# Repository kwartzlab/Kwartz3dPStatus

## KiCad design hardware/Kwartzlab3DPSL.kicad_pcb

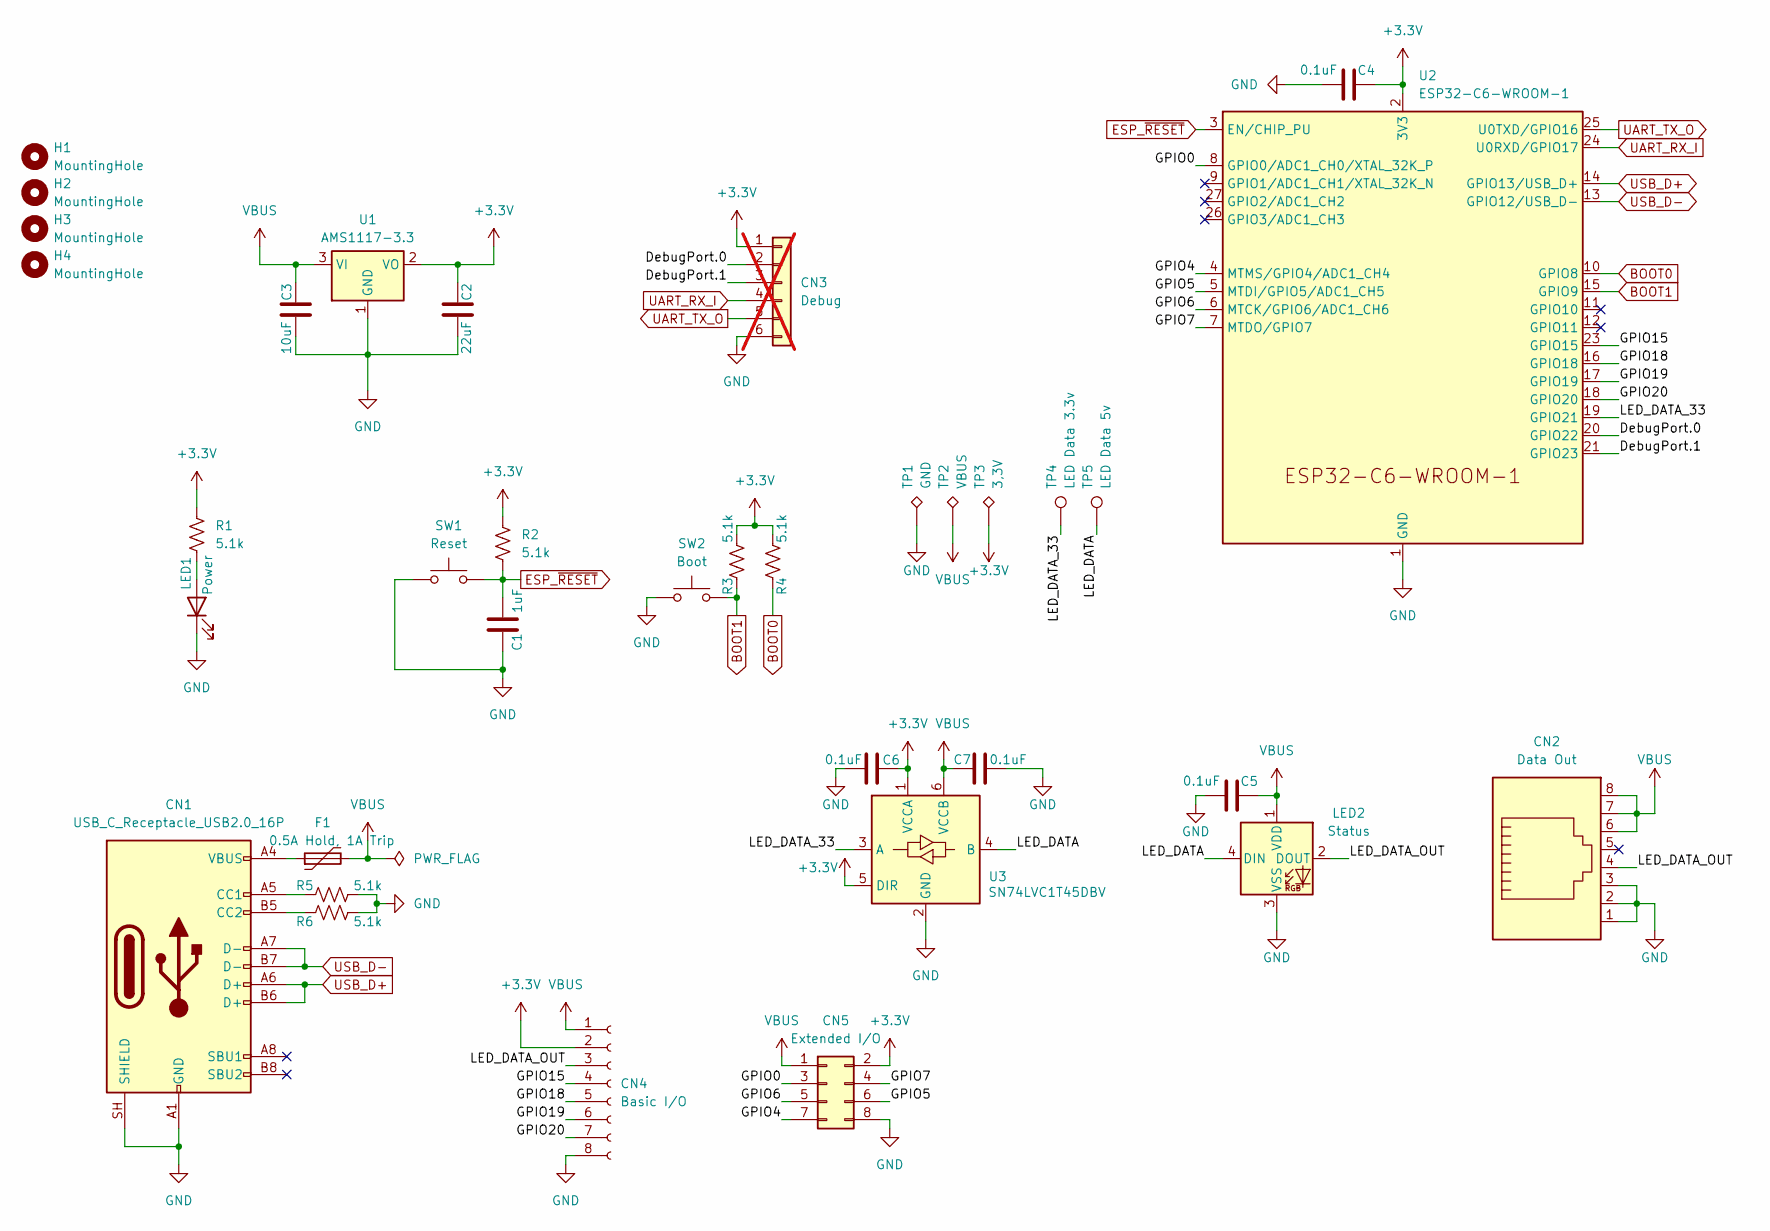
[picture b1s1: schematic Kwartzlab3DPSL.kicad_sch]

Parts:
C1: 1uF; C_0603_1608Metric
C2: 22uF; C_0603_1608Metric
C3: 10uF; C_0603_1608Metric
C4, C5, C6, C7: 0.1uF; C_0603_1608Metric
CN1: USB_C_Receptacle_USB2.0_16P; USB_C_Receptacle_G-Switch_GT-USB-7010ASV
CN2: Data Out; RJ45_AdamTech_MTJ-881X1
CN3: Debug; PinHeader_2x03_P1.00mm_Vertical; not fitted
CN4: Basic I/O; PhoenixContact_MC_1,5_8-G-3.5_1x08_P3.50mm_Horizontal
CN5: Extended I/O; PinHeader_2x04_P2.54mm_Vertical_SMD
F1: 0.5A Hold, 1A Trip; Fuse_2920_7451Metric
H1, H2, H3, H4: MountingHole; MountingHole_2.7mm_M2.5_ISO14580
LED1: Power; LED_0603_1608Metric
LED2: Status; LED_WS2812B_PLCC4_5.0x5.0mm_P3.2mm
R1, R2, R3, R4, R5, R6: 5.1k; R_0603_1608Metric
SW1: Reset; SW_SPST_PTS645Sx43SMTR92
SW2: Boot; SW_SPST_PTS645Sx43SMTR92
TP1: GND; TestPoint_THTPad_1.0x1.0mm_Drill0.5mm
TP2: VBUS; TestPoint_Pad_2.0x2.0mm
TP3: 3,3V; TestPoint_Pad_2.0x2.0mm
TP4: LED Data 3.3v; TestPoint_Pad_2.0x2.0mm
TP5: LED Data 5v; TestPoint_Pad_2.0x2.0mm
U1: AMS1117-3.3; SOT-223-3_TabPin2
U2: ESP32-C6-WROOM-1
U3: SN74LVC1T45DBV; SOT-23-6

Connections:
+3.3V: C2.2, C4.2, C6.2, CN3.1, CN4.2, CN5.2, R1.1, R2.1, R3.1, R4.1, TP3.1 (1_1), U1.2 (VO), U2.2 (3V3), U3.1 (VCCA), U3.5 (DIR)
/DebugPort.0: CN3.2, U2.20 (GPIO22)
/DebugPort.1: CN3.3, U2.21 (GPIO23)
/GPIO0: CN5.3, U2.8 (GPIO0/ADC1_CH0/XTAL_32K_P)
/GPIO4: CN5.7, U2.4 (MTMS/GPIO4/ADC1_CH4)
/GPIO5: CN5.6, U2.5 (MTDI/GPIO5/ADC1_CH5)
/GPIO6: CN5.5, U2.6 (MTCK/GPIO6/ADC1_CH6)
/GPIO7: CN5.4, U2.7 (MTDO/GPIO7)
/GPIO15: CN4.4, U2.23 (GPIO15)
/GPIO18: CN4.5, U2.16 (GPIO18)
/GPIO19: CN4.6, U2.17 (GPIO19)
/GPIO20: CN4.7, U2.18 (GPIO20)
/LED_DATA: LED2.4 (DIN), TP5.1 (1_1), U3.4 (B)
/LED_DATA_33: TP4.1 (1_1), U2.19 (GPIO21), U3.3 (A)
/LED_DATA_OUT: CN2.4, CN4.3, LED2.2 (DOUT)
BOOT0: R4.2, U2.10 (GPIO8)
BOOT1: R3.2, SW2.2, U2.15 (GPIO9)
ESP_~RESET: C1.1, R2.2, SW1.2, U2.3 (EN/CHIP_PU)
GND: C1.2, C2.1, C3.1, C4.1, C5.1, C6.1, C7.1, CN1.A1 (GND), CN1.A12 (GND), CN1.B1 (GND), CN1.B12 (GND), CN1.SH (SHIELD), CN2.1, CN2.2, CN2.3, CN3.6, CN4.8, CN5.8, LED1.1 (K), LED2.3 (VSS), R5.2, R6.2, SW1.1, SW2.1, TP1.1 (1_1), U1.1 (GND), U2.1 (GND), U2.28 (GND), U2.29 (GND), U3.2 (GND)
unnamed: CN1.A5 (CC1), R5.1
unnamed: CN1.B5 (CC2), R6.1
unnamed: CN1.A4 (VBUS), CN1.A9 (VBUS), CN1.B4 (VBUS), CN1.B9 (VBUS), F1.1
unnamed: LED1.2 (A), R1.2
UART_RX_I: CN3.4, U2.24 (U0RXD/GPIO17)
UART_TX_O: CN3.5, U2.25 (U0TXD/GPIO16)
USB_D+: CN1.A6 (D+), CN1.B6 (D+), U2.14 (GPIO13/USB_D+)
USB_D-: CN1.A7 (D-), CN1.B7 (D-), U2.13 (GPIO12/USB_D-)
VBUS: C3.2, C5.2, C7.2, CN2.6, CN2.7, CN2.8, CN4.1, CN5.1, F1.2, LED2.1 (VDD), TP2.1 (1_1), U1.3 (VI), U3.6 (VCCB)

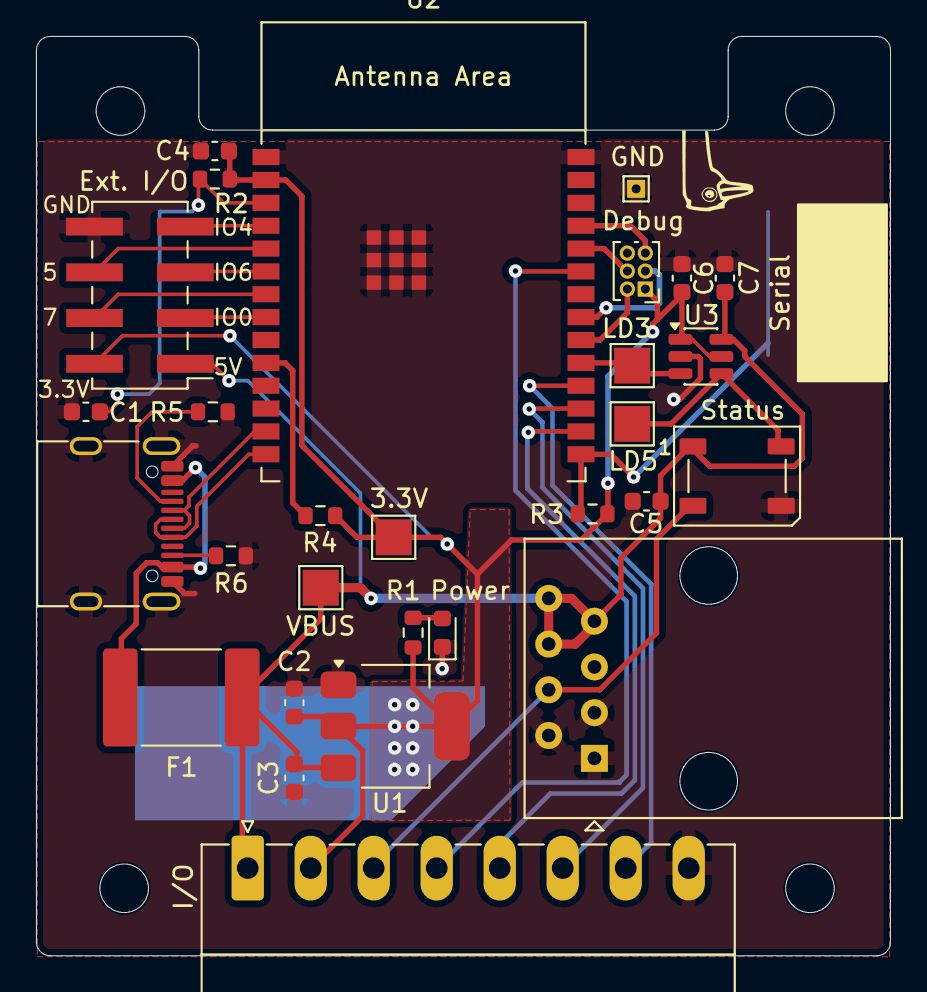
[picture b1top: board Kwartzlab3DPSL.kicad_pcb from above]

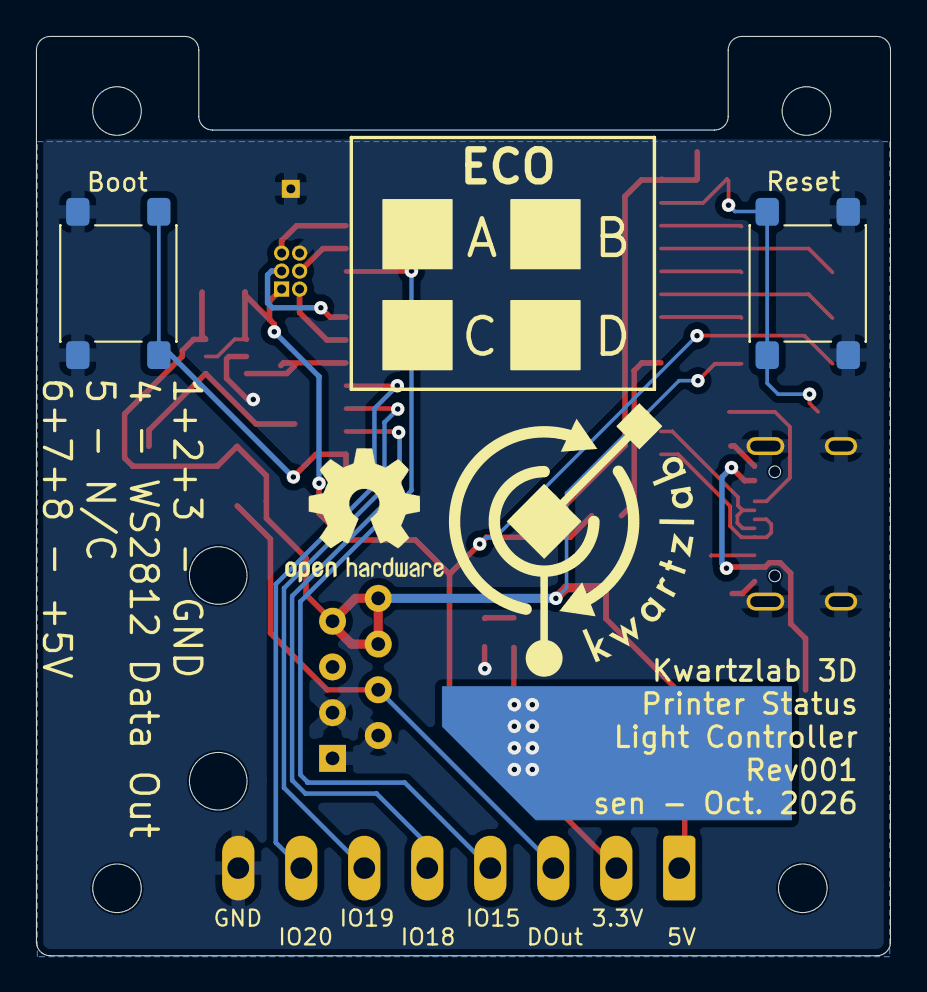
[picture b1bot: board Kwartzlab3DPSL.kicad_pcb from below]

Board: 2 copper layers, 47.4 x 51.1 mm, 35 parts (2 on the bottom side), 28 nets.

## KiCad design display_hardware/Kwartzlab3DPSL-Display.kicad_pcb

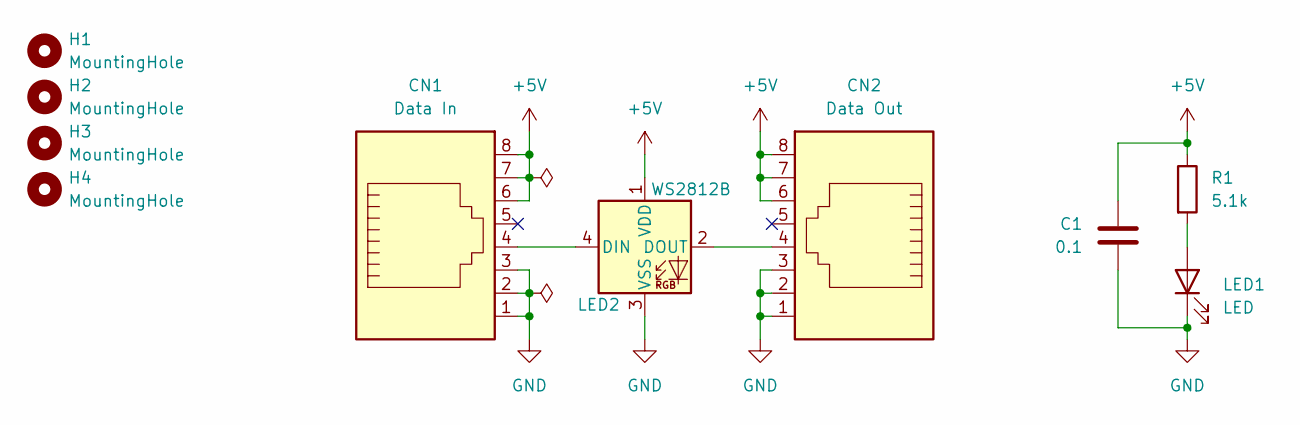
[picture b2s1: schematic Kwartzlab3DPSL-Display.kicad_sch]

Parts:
C1: 0.1; C_0603_1608Metric
CN1: Data In; RJ45_AdamTech_MTJ-881X1
CN2: Data Out; RJ45_AdamTech_MTJ-881X1
H1, H2, H3, H4: MountingHole; MountingHole_3.2mm_M3_ISO14580
LED1: LED; LED_0603_1608Metric
LED2: WS2812B; LED_WS2812B_PLCC4_5.0x5.0mm_P3.2mm
R1: 5.1k; R_0603_1608Metric

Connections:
+5V: C1.1, CN1.6, CN1.7, CN1.8, CN2.6, CN2.7, CN2.8, LED2.1 (VDD), R1.1
GND: C1.2, CN1.1, CN1.2, CN1.3, CN2.1, CN2.2, CN2.3, LED1.1 (K), LED2.3 (VSS)
unnamed: LED1.2 (A), R1.2
unnamed: CN1.4, LED2.4 (DIN)
unnamed: CN2.4, LED2.2 (DOUT)

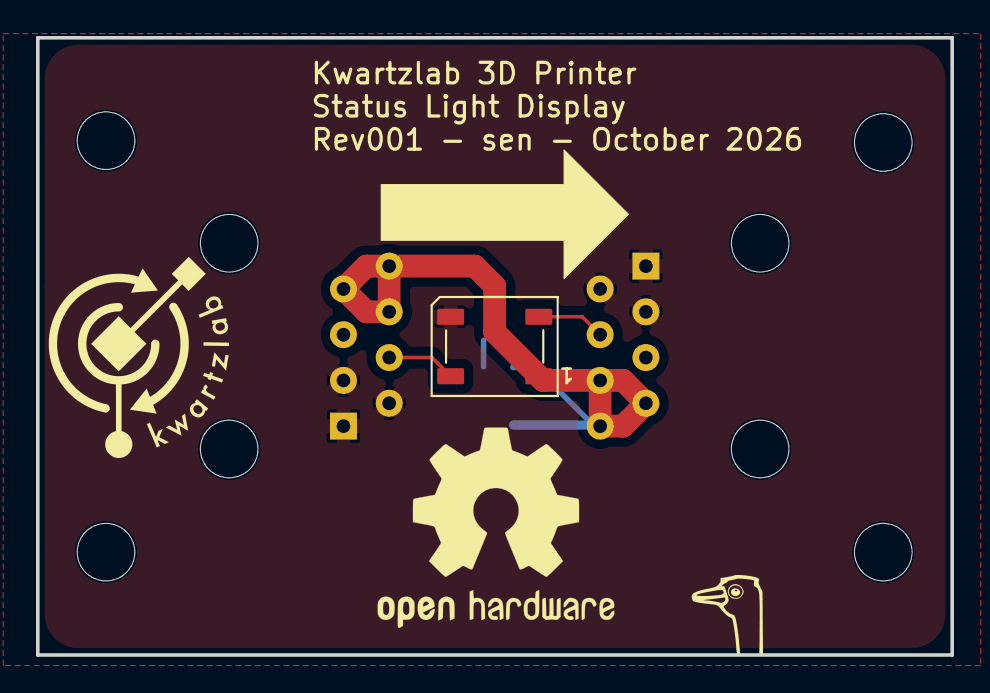
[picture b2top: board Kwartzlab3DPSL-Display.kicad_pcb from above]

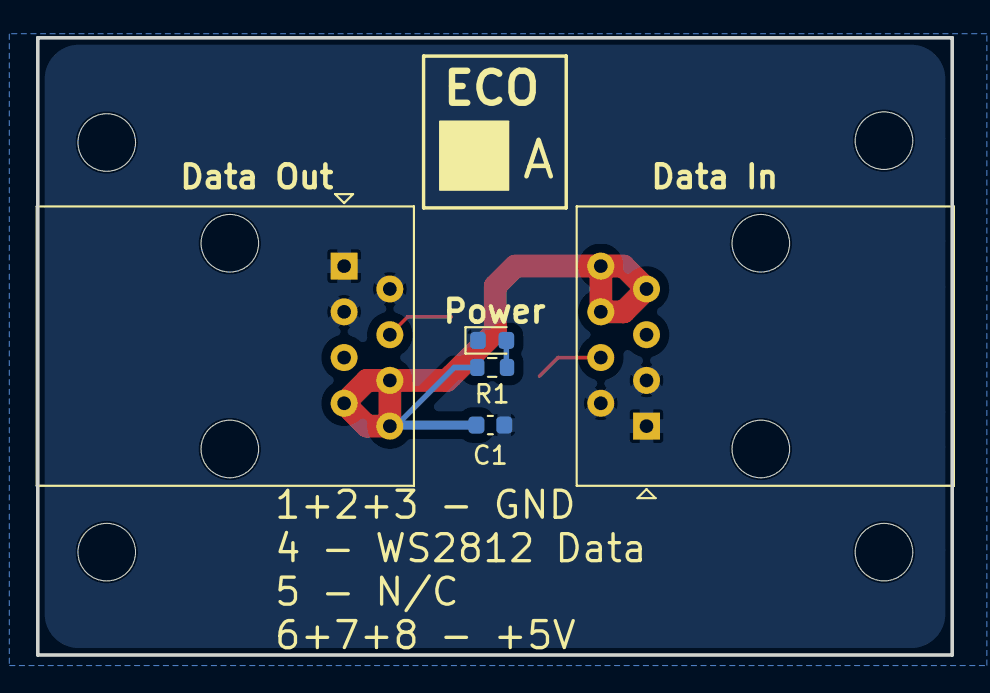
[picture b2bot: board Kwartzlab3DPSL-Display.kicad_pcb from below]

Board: 2 copper layers, 50.8 x 34.3 mm, 10 parts (5 on the bottom side), 5 nets.
